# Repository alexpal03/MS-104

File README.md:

# MS-104
Repositorio dedicado a recopilar información y registrar avances sobre la restauración de la MS-104

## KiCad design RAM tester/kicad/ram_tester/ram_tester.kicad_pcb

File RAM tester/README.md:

# Testeador de RAM de 64kbytes para MS101 - MS104

El testeador tiene capacidad de verificar hasta 64kB de memoria RAM, pero lo hace por sectores conformados por 8kbytes.
En total hay 8 sectores.

La decisión de usar esta delimitación de sectores es debido al mapeo de memoria de la 101-104:

|Sector| Direcciones |
| ---- | --------- |
|  1   |0000 - 1FFF|
|  2   |2000 - 3FFF|
|  3   |4000 - 5FFF|
|  4   |6000 - 7FFF|
|  5   |8000 - 9FFF|
|  6   |A000 - BFFF|
|  7   |C000 - DFFF|
|  8   |E000 - FFFF|

## Modo de uso

1. Conectar el testeador de ram en el algún espacio del rack de tarjetas, preferiblemene en el espacio del CPU.
2. Hacer doble click en el botón para entrar a la configuración, donde se podrá seleccionar el sector a testear. Para moverse por las opciones se debe hacer un solo click, y una vez que se seleccione el sector deseado se vuelve a presionar doble click para volver al inicio.
3. Una vez en el inicio, se comienza el test con un solo click
4. Al finalizar el test, aparece la primera pantalla de resultado, que indica la cantidad de direcciones donde hubo errores de lectura. Con un click se pasa a la siguiente pantalla, donde se muestra con mayor detalle los bits que tuvieron fallas organizados en bloques de 1kbyte. Ejemplo:

    ```
    7F 00 00 00
    00 50 00 00
    ```
    El `7F` que en binario es `01111111`, significa que en el primer bloque de 1kbyte fallaron todos los bits a excepción del más significativo.
    El `50` que en binario es `01010000` significa que en el sexto bloque de 1kbyte solo hay fallas en el B6 y B4.

    Esta subdivisión es útil porque tanto los integrados de RAM de la 101 y la 104 son de 1024 direcciones. De esta forma se puede localizar mucho más fácil la falla. Ej: si todos los bloques de 1kbyte fallan en el mismo bit, es probable que la falla sea del buffer de datos, y no de las RAM.

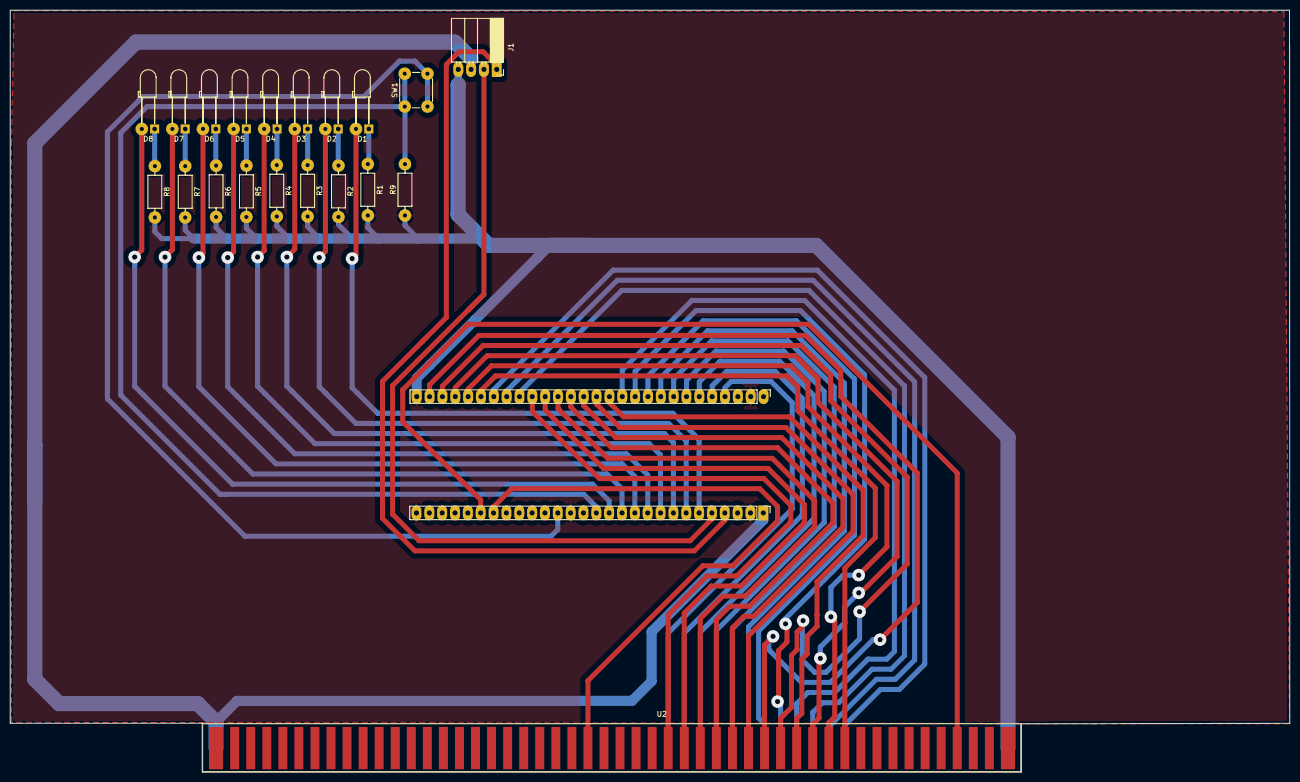
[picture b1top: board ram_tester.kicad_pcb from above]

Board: 2 copper layers, 253.0 x 150.6 mm, 21 parts (0 on the bottom side), 48 nets.

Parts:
D1, D2, D3, D4, D5, D6, D7, D8: LED; LED_D3.0mm_Horizontal_O6.35mm_Z10.0mm
J1: Conn_01x04_Male; PinSocket_1x04_P2.54mm_Horizontal
R1, R2, R3, R4, R5, R6, R7, R8: 670; R_Axial_DIN0207_L6.3mm_D2.5mm_P10.16mm_Horizontal
R9: 1000; R_Axial_DIN0207_L6.3mm_D2.5mm_P10.16mm_Horizontal
SW1: SW_Push; SW_PUSH_6mm_H5mm
U1: fubarino_sd
U2: s100

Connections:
+3.3V: SW1.2, U1.3 (3.3V), U1.31 (3.3V), U1.45 (3.3V)
+5V: J1.3, U1.29 (vin), U2.1, U2.51
GND: J1.4, R1.2, R2.2, R3.2, R4.2, R5.2, R6.2, R7.2, R8.2, R9.1, U1.2 (GND), U1.28 (GND), U1.30 (GND), U1.44 (GND), U1.56 (GND), U2.50, U2.100
unnamed: D1.2 (A), U1.34 (44/A0)
unnamed: D1.1 (K), R1.1
unnamed: D2.2 (A), U1.35 (43/A1)
unnamed: D2.1 (K), R2.1
unnamed: D3.2 (A), U1.36 (42/A2)
unnamed: D3.1 (K), R3.1
unnamed: D4.2 (A), U1.37 (41/A3)
unnamed: D4.1 (K), R4.1
unnamed: D5.2 (A), U1.38 (40/A4)
unnamed: D5.1 (K), R5.1
unnamed: D6.2 (A), U1.39 (39/A5)
unnamed: D6.1 (K), R6.1
unnamed: D7.2 (A), U1.40 (38/A6)
unnamed: D7.1 (K), R7.1
unnamed: D8.2 (A), U1.41 (37/A7)
unnamed: D8.1 (K), R8.1
unnamed: J1.1, U1.32 (29/TX)
unnamed: J1.2, U1.33 (28/RX)
unnamed: U1.4 (0), U2.79
unnamed: U1.5 (1), U2.80
unnamed: U1.6 (2), U2.81
unnamed: U1.7 (3), U2.82
unnamed: U1.8 (4), U2.83
unnamed: U1.9 (5), U2.84
unnamed: U1.10 (6), U2.85
unnamed: U1.11 (7), U2.86
unnamed: U1.12 (8), U2.87
unnamed: U1.13 (9), U2.37
unnamed: U1.14 (10), U2.34
unnamed: U1.15 (11), U2.33
unnamed: U1.16 (12), U2.32
unnamed: U1.17 (13), U2.31
unnamed: U1.18 (14), U2.30
unnamed: U1.19 (15), U2.29
unnamed: U1.20 (16), U2.88
unnamed: U1.21 (17), U2.89
unnamed: U1.22 (18), U2.90
unnamed: U1.23 (19), U2.40
unnamed: U1.24 (20), U2.39
unnamed: U1.25 (21), U2.38
unnamed: U1.26 (22), U2.36
unnamed: U1.27 (23), U2.35
unnamed: U1.51 (30/A14), U2.47
unnamed: U1.50 (31/A13), U2.24
unnamed: R9.2, SW1.1, U1.42 (36/A8)

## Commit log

2025-06-06 Rename fubarino sd.pdf to RAM tester/fubarino sd.pdf
2025-06-06 Rename fubarino-github.txt to RAM tester/fubarino-github.txt
2025-06-06 Rename RAM tester/s100.kicad_sym to RAM tester/kicad/ram_tester/s100.kicad_sym
2025-09-18 Rename ram_tester.ino to ram_tester_v1-0.ino
2025-09-24 Rename ram_tester_v1-0.ino to ram_tester.ino
